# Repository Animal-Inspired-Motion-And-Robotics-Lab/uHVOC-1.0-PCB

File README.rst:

Univeral High Voltage Optimized Converter (uHVOC)
=================================================

===========
Description
===========

uHVOC is a multi-output high voltage DC-DC converter designed for use as an evaluation platform
or in any scenario that needs multiple high voltages. The board can be used without any external
controllers thanks to an integrated HV9150 DC-DC controller, but optionally can be controlled with 
a microcontroller or Raspberry Pi through the integrated `Proto Pi`_ connector.

.. _Proto Pi: https://github.com/Animal-Inspired-Motion-And-Robotics-Lab/Proto-Pi-Board
.. image:: uHVOC_Concept.png

=========
Features
=========

#. Generates three high voltages at Vout, 2Vout and 4Vout.
#. Voltage, duty cycle, switching frequency programmable via potentiometer or Proto-Pi.  

=========
Examples
=========

===========
Configuring
===========

=========
Features
=========

====
Todos
====

#. Figure out capacitive load designed and determine if I want it.
#. Determine if I want to add 2x electroadhesion H-bridges.
#. Figure out how to include microcontroller connection.
#. Design voltage multiplier module.

=======
License
=======

Attribution-ShareAlike 4.0 International

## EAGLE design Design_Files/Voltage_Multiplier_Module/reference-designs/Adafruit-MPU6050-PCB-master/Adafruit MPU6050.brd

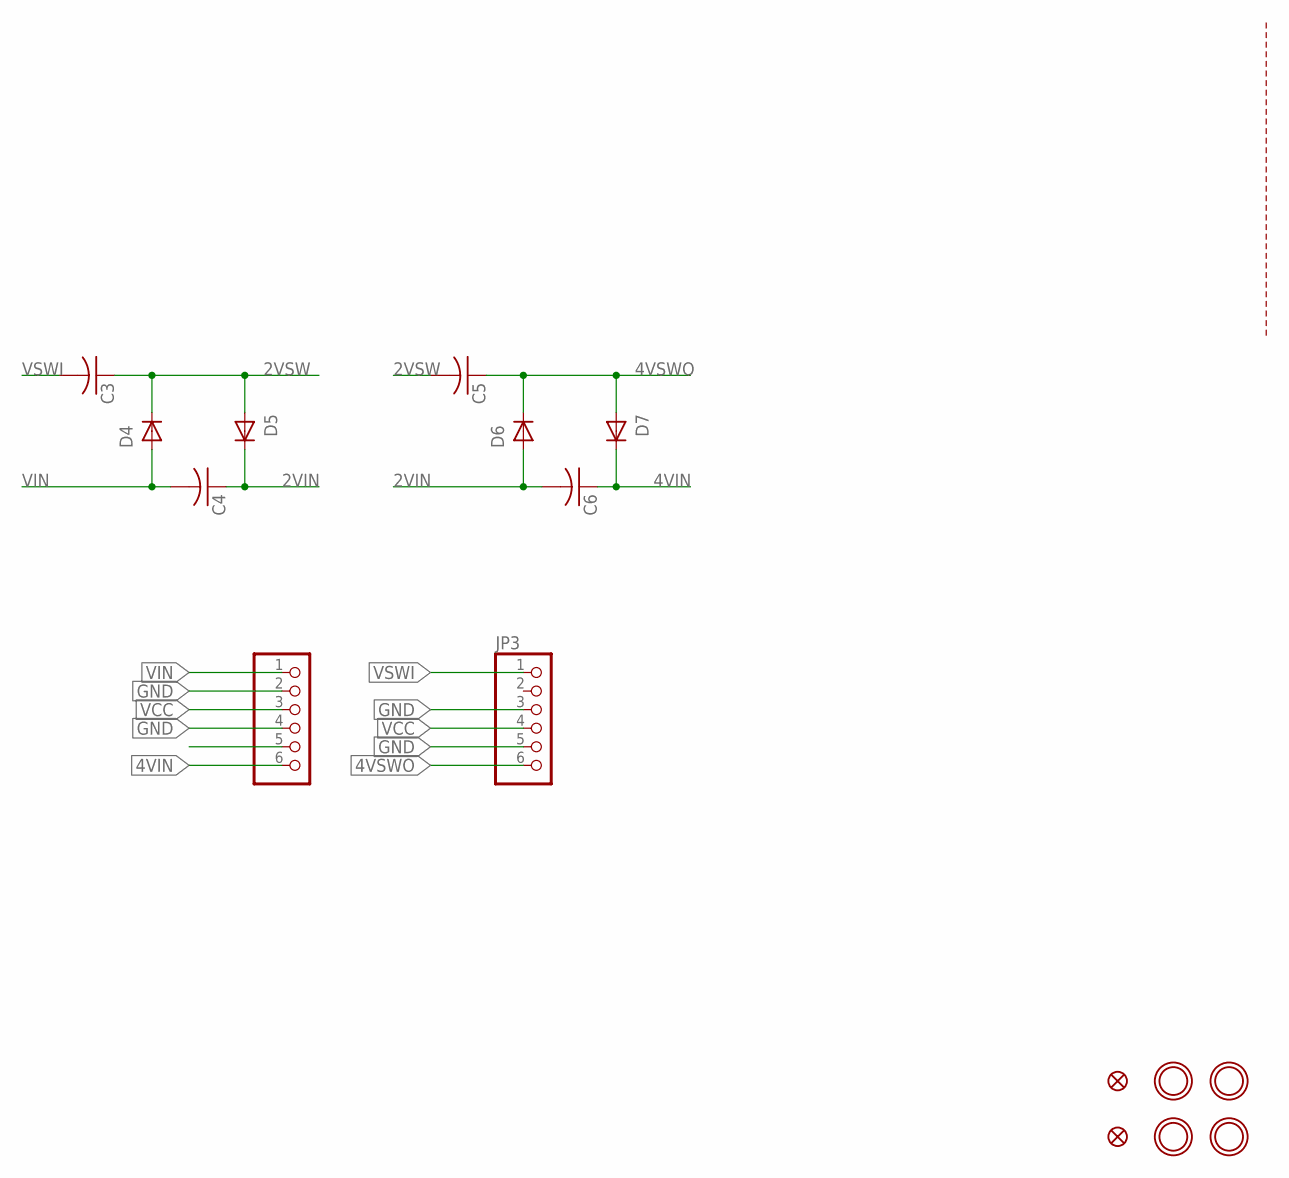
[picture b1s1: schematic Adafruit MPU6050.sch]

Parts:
C3, C4, C5, C6: C-USC0603; C0603
D4, D5, D6, D7: DI-BAS21LD; SOD882D
FID3, FID4: FIDUCIAL_1MM
JP2: HEADER-1X6ROUND; 1X06_ROUND
JP3: HEADER-1X670MIL; 1X06_ROUND_70
U$39, U$40, U$42, U$43: MOUNTINGHOLE2.5; MOUNTINGHOLE_2.5_PLATED

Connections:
2VIN: C4.1, C6.2, D5.K, D6.A
2VSW: C3.1, C5.2, D4.K, D5.A
4VIN: C6.1, D7.K, JP2.6
4VSWO: C5.1, D6.K, D7.A, JP3.6
GND: JP2.2, JP2.4, JP3.3, JP3.5
VCC: JP2.3, JP3.4
VIN: C4.2, D4.A, JP2.1
VSWI: C3.2, JP3.1

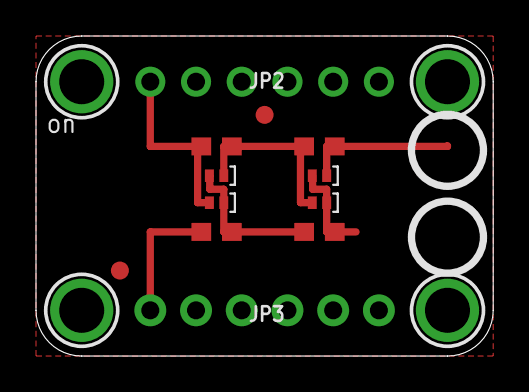
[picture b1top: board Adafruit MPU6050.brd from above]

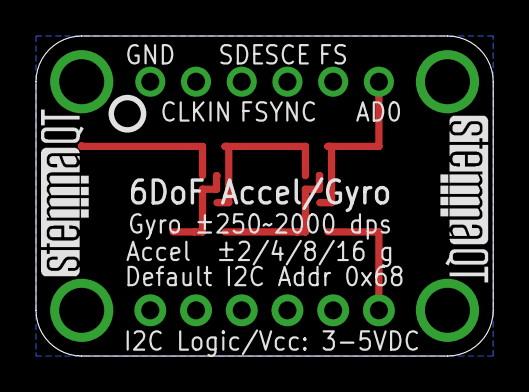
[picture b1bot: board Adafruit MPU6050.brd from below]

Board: 2 copper layers, 25.4 x 17.8 mm, 19 parts (3 on the bottom side), 8 nets.

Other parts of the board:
U$46: PCBFEAT-REV-040
U$47, U$48: STEMMAQT

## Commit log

2022-05-18 Updated README.rst
2022-05-20 Started voltage multiplier module
2022-05-31 Added micropump reference design

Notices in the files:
parts and their libraries:
microbuilder: This work is placed in the public domain, and may be freely used for commercial and non-commercial work with the following conditions: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
